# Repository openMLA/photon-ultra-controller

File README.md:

# Photon Ultra DLP controller

This repository contains PCB design files and code to control the UV projector found on the [Anycubic Photon Ultra](https://store.anycubic.com/products/photon-ultra). It also serves as a general example of how to send data to and control the [DCLP1438 DMD controller](https://www.ti.com/product/DLPC1438) through the parallel video interface.

The replacement board allows users to generate the signals required for the *DLP controller board* (designed by eViewTek) & DMD that comes with the photon ultra. It does not capture the full functionality of the Anycubic mainboard as it does not control the interface LCD, control the mechanics (stepper motor) or run any resin 3D printer slicer software. It **only** controls the DLP projector with an arbitrary 8-bit 1280x720 image. Exposure time can be set per image. It is also possible to play video on the projector, if that is something you have a use for. [Video has been tested up to 30Hz](https://github.com/openMLA/photon-ultra-controller/issues/1#issuecomment-2057936067), but should work up to 60Hz.

This project might be of interest to you if you **own a photon ultra** and are interested in either

1. Using the photon ultra for PCB fabrication (use the DLP to expose a photoresist)
2. Are looking to use a DMD for other applications but are not ready to build your own controller board.

If you are interested in learning more about the Photon Ultra, you can find more information on [this photon ultra teardown blog post](https://nemoandrea.github.io/blog/Anycubic_DLP_teardown/). More images are available on request.

> If you have a projector using the DLPC1438 that uses an SPI interface (rather than parallel video), then you can check out the [PCB design and implementation for the Elegoo-mars-4 DLP](https://github.com/openMLA/elegoo-mars-4-dlp-controller) projector.

### PCB

The PCB is designed around the standard 40-pin header present on the main Raspberry pi boards. Have a look at the required pins in the schematic to determine how to implement it for other boards.

The PCB readme also contains a breakdown of parts and cost in the BOM. The total PCB + raspberry pi zero 2 cost is around **65 euro** including tax. 

Keep in mind that you would also need to get your hands on the PCB and UV projector found in an Anycubic Photon Ultra. When it was still being sold in stores, that printer went for around **300 euros**. Second-hand options would be attractive, as the projector is unlikely to be significantly worn or covered in layers of sticky resin. Alternatively you can try contacting eViewTek and source the optical engine and driver board directly.

The PCB has been assembled and verified. Evaluated functionality:

* Powering a Raspberry Pi Zero 2
* Powering the eViewTek board
* software i2c communication (with DLPC1438)
* video display via the parallel interface on the DMD
* Status LED (not currently used in code, but they light up)

Not tested:

* The extra GPIO pins on top (including SPI)
* Stemma QT connection

### Context

This work was developed as part of the [openMLA project](https://github.com/openMLA), where the goal is to build an open hardware lithography system. Eventually an open hardware DLP controller board will be published as part of openMLA, but this represents an intermediate step. 

An earlier attempt at realising the right output format using a rp2040 was partially successful (image display was working), but memory limitations lead to the archiving of that project and the continuation with the current approach, The archived version [is still available](https://github.com/openMLA/photon-ultra-controller-rp2040) for those interested.

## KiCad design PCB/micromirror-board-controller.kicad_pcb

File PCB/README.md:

### PCB design

The design is tested with a raspberry pi zero 2, but in principle any Raspberry pi will work. The hardware pins should all be shared, but some changes in raspberry Pi OS may break stuff for newer boards. 

See [the schematic](micromirror-board-controller.pdf) for more info.

### Assembly

Most components are SMD, and the mouser links can be found in the basic [BOM](BOM.csv). In addition to the components of the BOM, you will also need some small wires to connect the USB data lines.

That 51-pin connector is a real pain to solder. For me going with a lower melting point solder and proper board heating made it manageable, but it's not the most enjoyable experience.

### BOM

The prices below include Dutch VAT tax (21%). 

| Description                      | Supplier         | Supplier Part Number | Amount | Total Cost | Comment                                      |
| -------------------------------- | ---------------- | -------------------- | ------ | ---------- | -------------------------------------------- |
| PCB manufacturing                | Aisler           |                      | 3      | 16.16      | MOC 3pcs                                     |
| Raspberry Pi Zero 2              | Mouser           | 358-SC0510           | 1      | 16.9       |                                              |
| Micro SD Card (32GB)             | Kiwi Electronics | TS32GUSDU1           | 1      | 10         | Whatever kind you want would work            |
| Raspberry pi header              | Kiwi Electronics | KW-2639              | 1      | 2          | or any basic, cheaper header                 |
| Raspberry pi header female       | Kiwi Electronics | KW-1650              | 1      | 1.5        |                                              |
| JST SH 4-pin                     | Mouser           | 474-PRT-16766        | 1      | 0.67       | Optional, allows i2c through  stemmaQT/QWIIC |
| Cui DC-DC converter              | Mouser           | 490-P78E05-1000      | 1      | 3.45       |                                              |
| Barreljack                       | Mouser           | 490-PJ-002B          | 1      | 0.79       |                                              |
| Schottky Diode                   | Mouser           | 771-PMEG1020EJ-T/R   | 1      | 0.29       |                                              |
| 100uF capacitor                  | Mouser           | 667-EEE-FN1E101UP    | 1      | 0.57       |                                              |
| 4.7k Ohm pullup resistor         | Mouser           | 667-ERA-8AEB472V     | 2      | 0.87       |                                              |
| 330 Ohm resistor                 | Mouser           | 667-ERA-8AEB331V     | 2      | 0.75       |                                              |
| Green LED                        | Mouser           | 710-150080VS75000    | 1      | 0.22       |                                              |
| Red LED                          | Mouser           | 710-150080RS75000    | 1      | 0.22       |                                              |
| 51-pin FPC connector             | Mouser           | 798-FH35C51S03SHW50  | 1      | 3.52       | not fun to solder                            |
| 3 -pin JST PH connector (10pack) | Mouser           | 485-4389             | 1      | 3.95       | Probably best to find the single-unit part   |
| 4-pin JST PH connector (10pack)  | Mouser           | 485-4390             | 1      | 3.95       | Probably best to find the single-unit part   |
|                                  |                  |                      |        |            |                                              |
| Total                            |                  |                      |        | 65.77      |                                              |

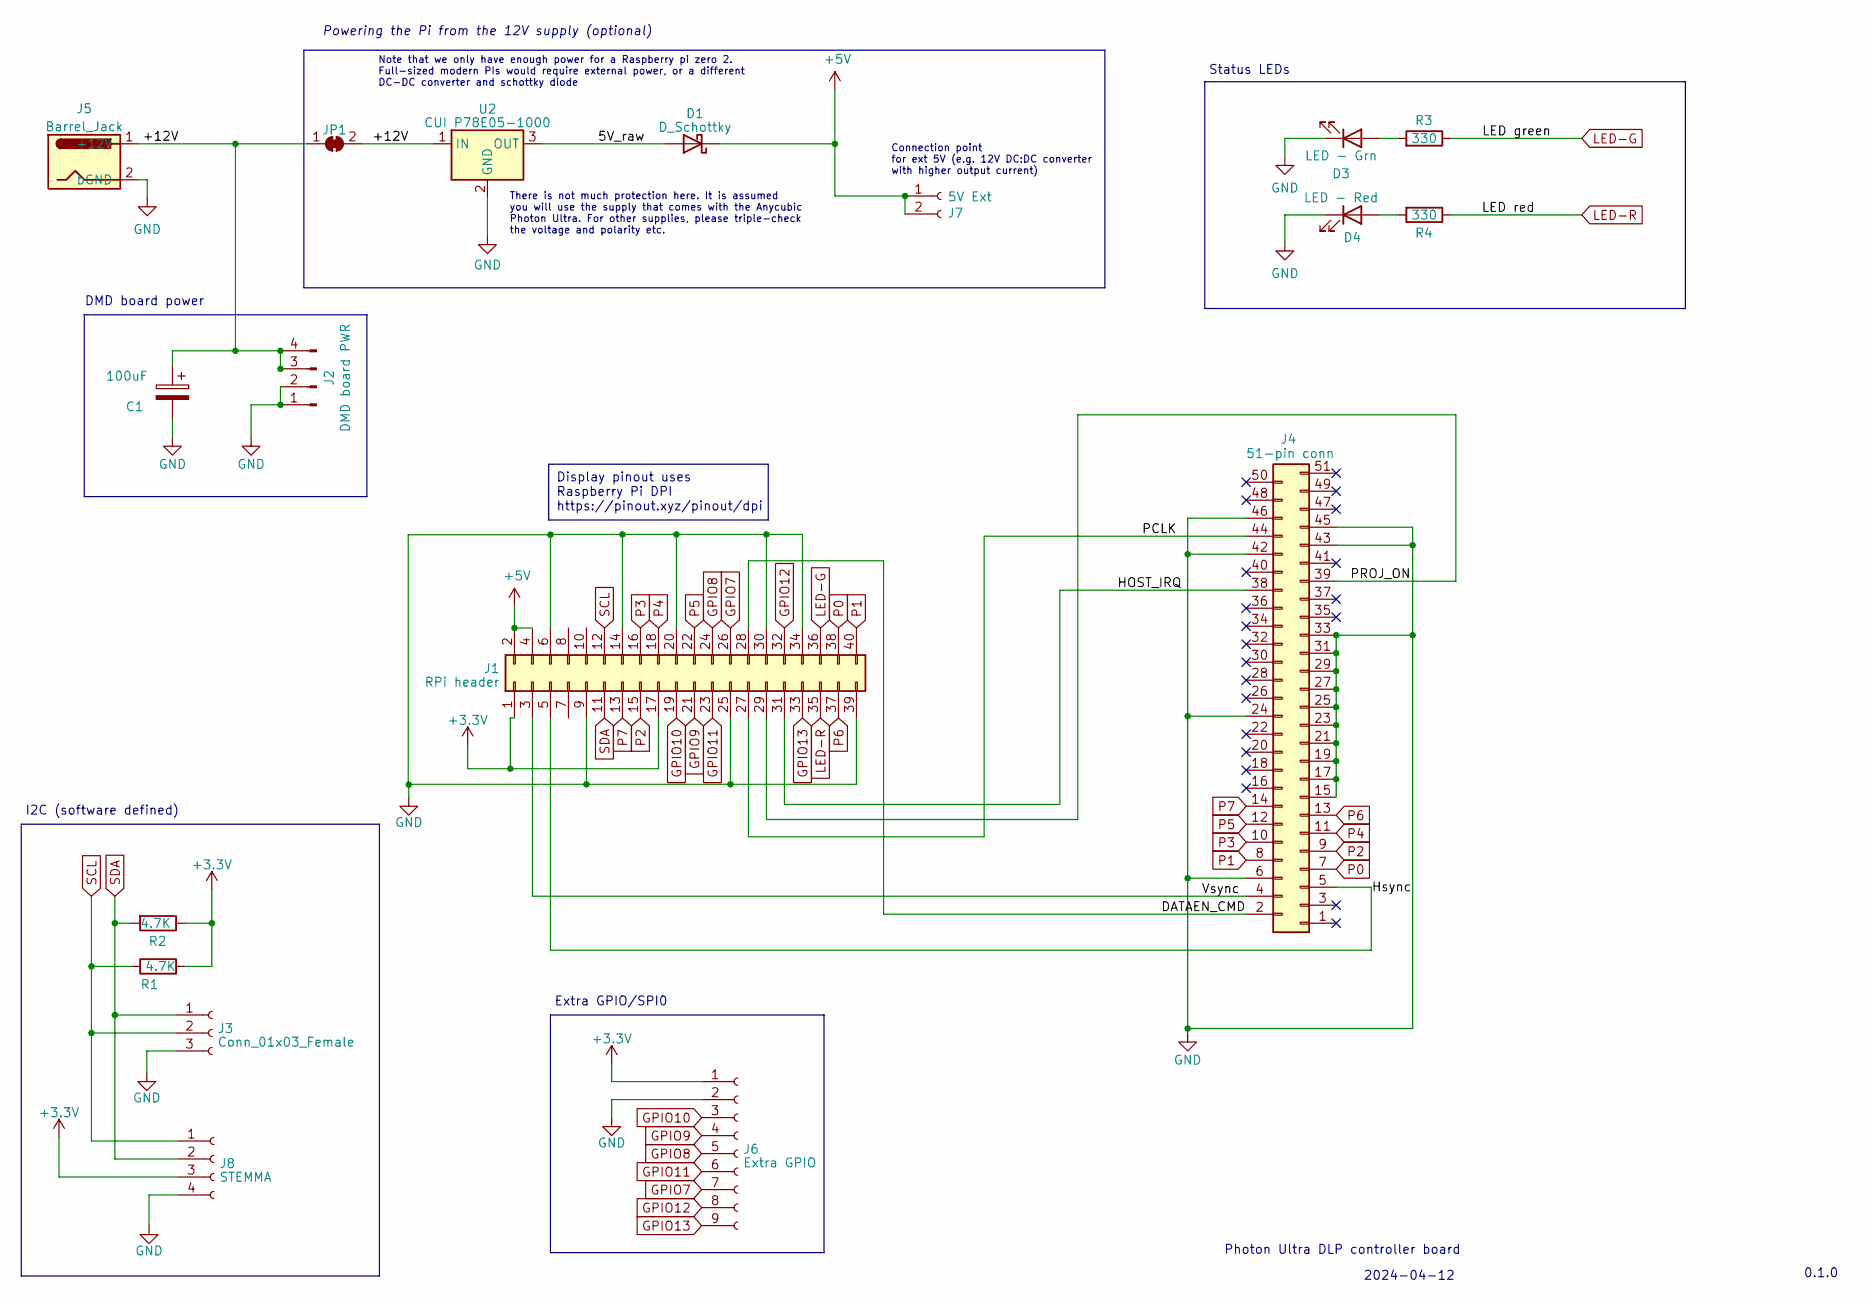
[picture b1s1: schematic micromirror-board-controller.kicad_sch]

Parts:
C1: 100uF; CP_Elec_6.3x7.7
D1: D_Schottky; D_SOD-323_HandSoldering; Mouser 771-PMEG1020EJ-T/R
D3: LED - Grn; LED_0805_2012Metric; Mouser 710-150080VS75000
D4: LED - Red; LED_0805_2012Metric; Mouser 710-150080RS75000
J1: RPi header; PinSocket_2x20_P2.54mm_Vertical
J2: DMD board PWR; JST_PH_B4B-PH-SM4-TB_1x04-1MP_P2.00mm_Vertical; Mouser 485-4390
J3: Conn_01x03_Female; JST_PH_B3B-PH-SM4-TB_1x03-1MP_P2.00mm_Vertical; Mouser 485-4389
J4: 51-pin conn; Molex_502250-5191_2Rows-51Pins-1MP_P0.60mm_Horizontal; Mouser-id 798-FH35C51S03SHW50
J5: Barrel_Jack; BarrelJack_GCT_DCJ200-10-A_Horizontal
J6: Extra GPIO; PinHeader_1x09_P2.54mm_Vertical
J7: 5V Ext; PinSocket_1x02_P2.54mm_Vertical
J8: STEMMA; JST_SH_BM04B-SRSS-TB_1x04-1MP_P1.00mm_Vertical; Mouser 474-PRT-16766
JP1: SolderJumper_2_Bridged; SolderJumper-2_P1.3mm_Open_TrianglePad1.0x1.5mm
R1: 4.7K; R_1206_3216Metric
R2: 4.7K; R_1206_3216Metric; Mouser 667-ERA-8AEB472V
R3, R4: 330; R_1206_3216Metric
U2: CUI P78E05-1000; Converter_DCDC_RECOM_R-78E-0.5_THT; Mouser 490-P78E05-1000

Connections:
+3.3V: J1.1, J1.17, J6.1, J8.3, R1.2, R2.1
+5V: D1.1 (K), J1.2, J1.4, J7.1, J7.2
/5V_raw: D1.2 (A), U2.3 (OUT)
/+12V: C1.1, J2.3, J2.4, J5.1 (+12V), JP1.1 (A), JP1.2 (B), U2.1 (IN)
/DATAEN_CMD: J1.28, J4.2 (DATAEN)
/HOST_IRQ: J1.31, J4.38 (HOST_IRQ)
/Hsync: J1.5, J4.5 (Hsync)
/PCLK: J1.27, J4.44 (PCLK)
/PROJ_ON: J1.29, J4.39 (GPIO_9)
/Vsync: J1.3, J4.4 (Vsync)
GND: C1.2, D3.1 (K), D4.1 (K), J1.6, J1.9, J1.14, J1.20, J1.25, J1.30, J1.34, J1.39, J2.1, J2.2, J3.3 (SDA), J4.6 (GND), J4.15 (GND), J4.17, J4.19, J4.21, J4.23, J4.24, J4.25, J4.27, J4.29, J4.31, J4.33, J4.42 (GND), J4.43 (GND), J4.45 (GND), J4.46 (GND), J5.2 (bGND), J6.2, J8.4, U2.2 (GND)
GPIO7: J1.26, J6.7
GPIO8: J1.24, J6.5
GPIO9: J1.21, J6.4
GPIO10: J1.19, J6.3
GPIO11: J1.23, J6.6
GPIO12: J1.32, J6.8
GPIO13: J1.33, J6.9
LED-G: J1.36, R3.1
LED-R: J1.35, R4.1
unnamed: D3.2 (A), R3.2
unnamed: D4.2 (A), R4.2
P0: J1.38, J4.7 (P1)
P1: J1.40, J4.8 (P0)
P2: J1.15, J4.9 (P3)
P3: J1.16, J4.10 (P2)
P4: J1.18, J4.11 (P5)
P5: J1.22, J4.12 (P4)
P6: J1.37, J4.13 (P7)
P7: J1.13, J4.14 (P6)
SCL: J1.12, J3.2 (SCL), J8.1, R1.1
SDA: J1.11, J3.1 (dGND), J8.2, R2.2

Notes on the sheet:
Display pinout uses Raspberry Pi DPI https://pinout.xyz/pinout/dpi
Extra GPIO/SPI0
There is not much protection here. It is assumed you will use the supply that comes with the Anycubic Photon Ultra. For other supplies, please triple-check the voltage and polarity etc.
Connection point for ext 5V (e.g. 12V DC:DC converter with higher output current)
Powering the Pi from the 12V supply (optional)
Status LEDs
Note that we only have enough power for a Raspberry pi zero 2. Full-sized modern PIs would require external power, or a different DC-DC converter and schottky diode
DMD board power
I2C (software defined)
Photon Ultra DLP controller board
2024-04-12
0.1.0

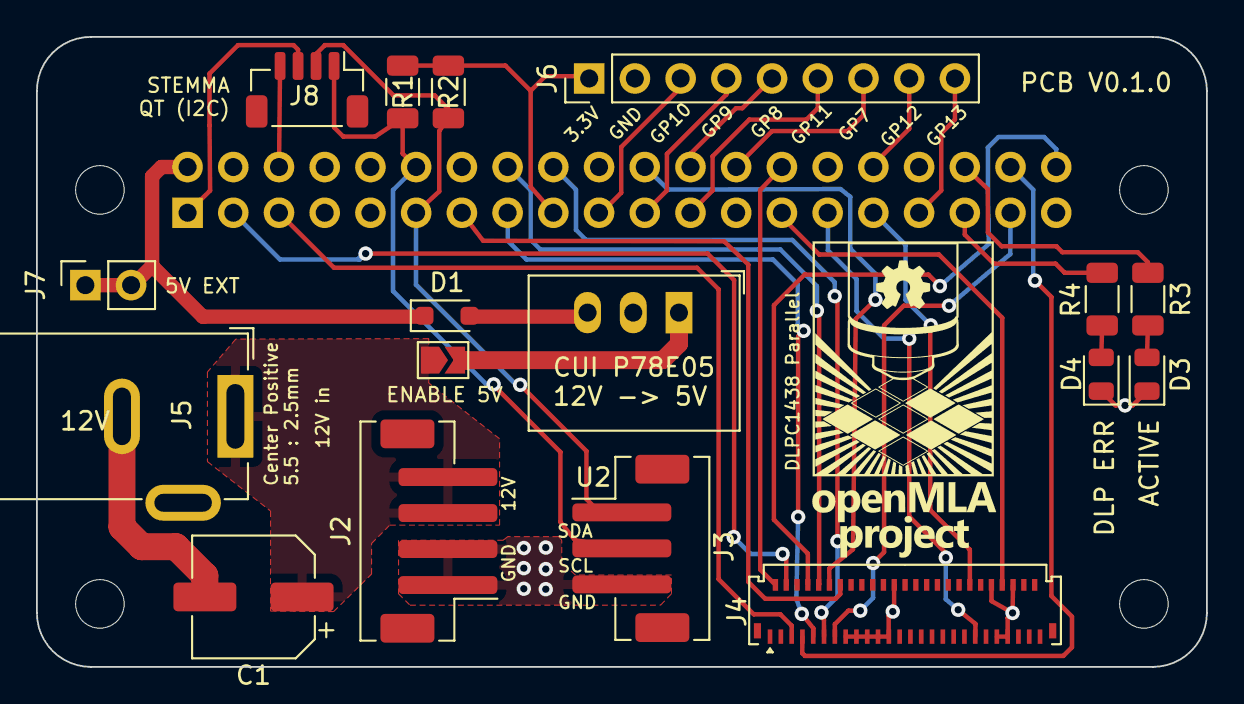
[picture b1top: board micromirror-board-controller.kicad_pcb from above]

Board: 2 copper layers, 65.0 x 35.0 mm, 22 parts (1 on the bottom side), 32 nets.

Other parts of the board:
MH1, MH2, MH3, MH4: MountingHole_2.7mm_M2.5

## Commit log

2024-04-12 Add intial PCB files
    Early draft of PCB
2024-04-12 fix markdown link
2024-04-13 functional parallel routing
2024-04-13 Completed routing and schematic
    Did all the routing for the board. Schematic also close to final.
2024-04-13 Added board silkscreen
    Added proper pin labels and project graphics
2024-04-13 Complete 3D model for PCB
    Added the 3D footprints for PCB. 3D view now displays everyhing as expected.
2024-04-13 fix silkscreen error
2024-04-13 Add BOM
    Add the bill of materials. Fixed some of the part number formatting in the schematic.
2024-04-14 Add minimal working code
    Add example python code and example image that shows off capability of approach.
2024-04-14 Remove old spi code block
    Fix issue with python code that still contained references to spi approach of elegoo mars 4 DLP code.
2024-04-14 Fix error in markdown and add clarification on status
2024-04-15 Working code for 8-bit grayscale
    Add working 8-bit grayscale code. Noticed that some of the pins are swapped; will fix in PCB design
2024-04-15 Add raspberry pi configuration instructions
    Added step-by-step instructions on how to configure raspberry pi to produce correct DPI output.
2024-04-16 Fix incorrect pinout for pixeldata
    Corrected the incorrect pinout of the pixeldata section of the FPC connector. Even and odd pins had to be switched (P0 <-> P1) etc. Fixes https://github.com/openMLA/photon-ultra-controller/issues/2.
2024-04-16 Update project status
    In main readme.md
2024-04-17 Move barrel jack slightly for enclosure purposes
    Moved the DC barrel jack on the PCB to facilitate the design of enclosures. The Connector now sticks out from the PCB board edge, allowing a 3D printed enclosure or similar to allow flush access to t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
2024-04-25 Add PCB evaluation results
    Confirm the testing and verification of the PCB. It is now safe to order the PCB and reproduce the project.
2024-04-25 Fix silkscreen error
    Extra GPIO pins had GND and 3.3V labels flipped. Corrected.
2024-04-26 Add simple printable enclosure
    Simple enclosure helps keep the cables from getting strained when the projector is moved. Needs a lid, but this is just a quick and simple design.
